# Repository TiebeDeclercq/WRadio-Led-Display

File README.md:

# WRadio LED Display
A custom-built LED display that showcases WRadio's logo with smooth animations and interactive brightness/animation controls via a built-in button.

## Hardware Overview
The design features a straightforward schematic controlled by an STM32F030F4P6TR microcontroller, providing reliable performance in a compact form factor and a cheap price.

## Assembly Instructions
### PCB Assembly
For soldering, refer to the included BOM (Bill of Materials) file. All components are 0805 package size for easy assembly.

### 3D Printed Enclosure
The enclosure consists of two main parts:

**Top Piece:** Requires a multi-color 3D printer or filament switching capability. The first few layers must be printed in white filament to allow proper light diffusion through the logo.

**Bottom Piece:** Choose between the standard base or the angled standing version depending on your preferred display orientation.

### Final Assembly
To assemble the enclosure, simply click the top and bottom pieces together. Make sure the USB-C port on the PCB aligns properly with the corresponding hole in the 3D printed top piece for easy access to power and programming.

## Software
The firmware is developed using STM32CubeIDE and includes:
- Multiple animation modes
- Adjustable brightness levels
- Save system in flash memory
- Button-controlled user interface

## Getting Started
1. Assemble the PCB using the provided BOM
2. 3D print the enclosure parts
3. Insert the PCB into the top piece, ensuring USB-C port alignment
4. Click the top piece into place
5. Flash the firmware using STM32CubeIDE
6. Enjoy your custom WRadio LED display!

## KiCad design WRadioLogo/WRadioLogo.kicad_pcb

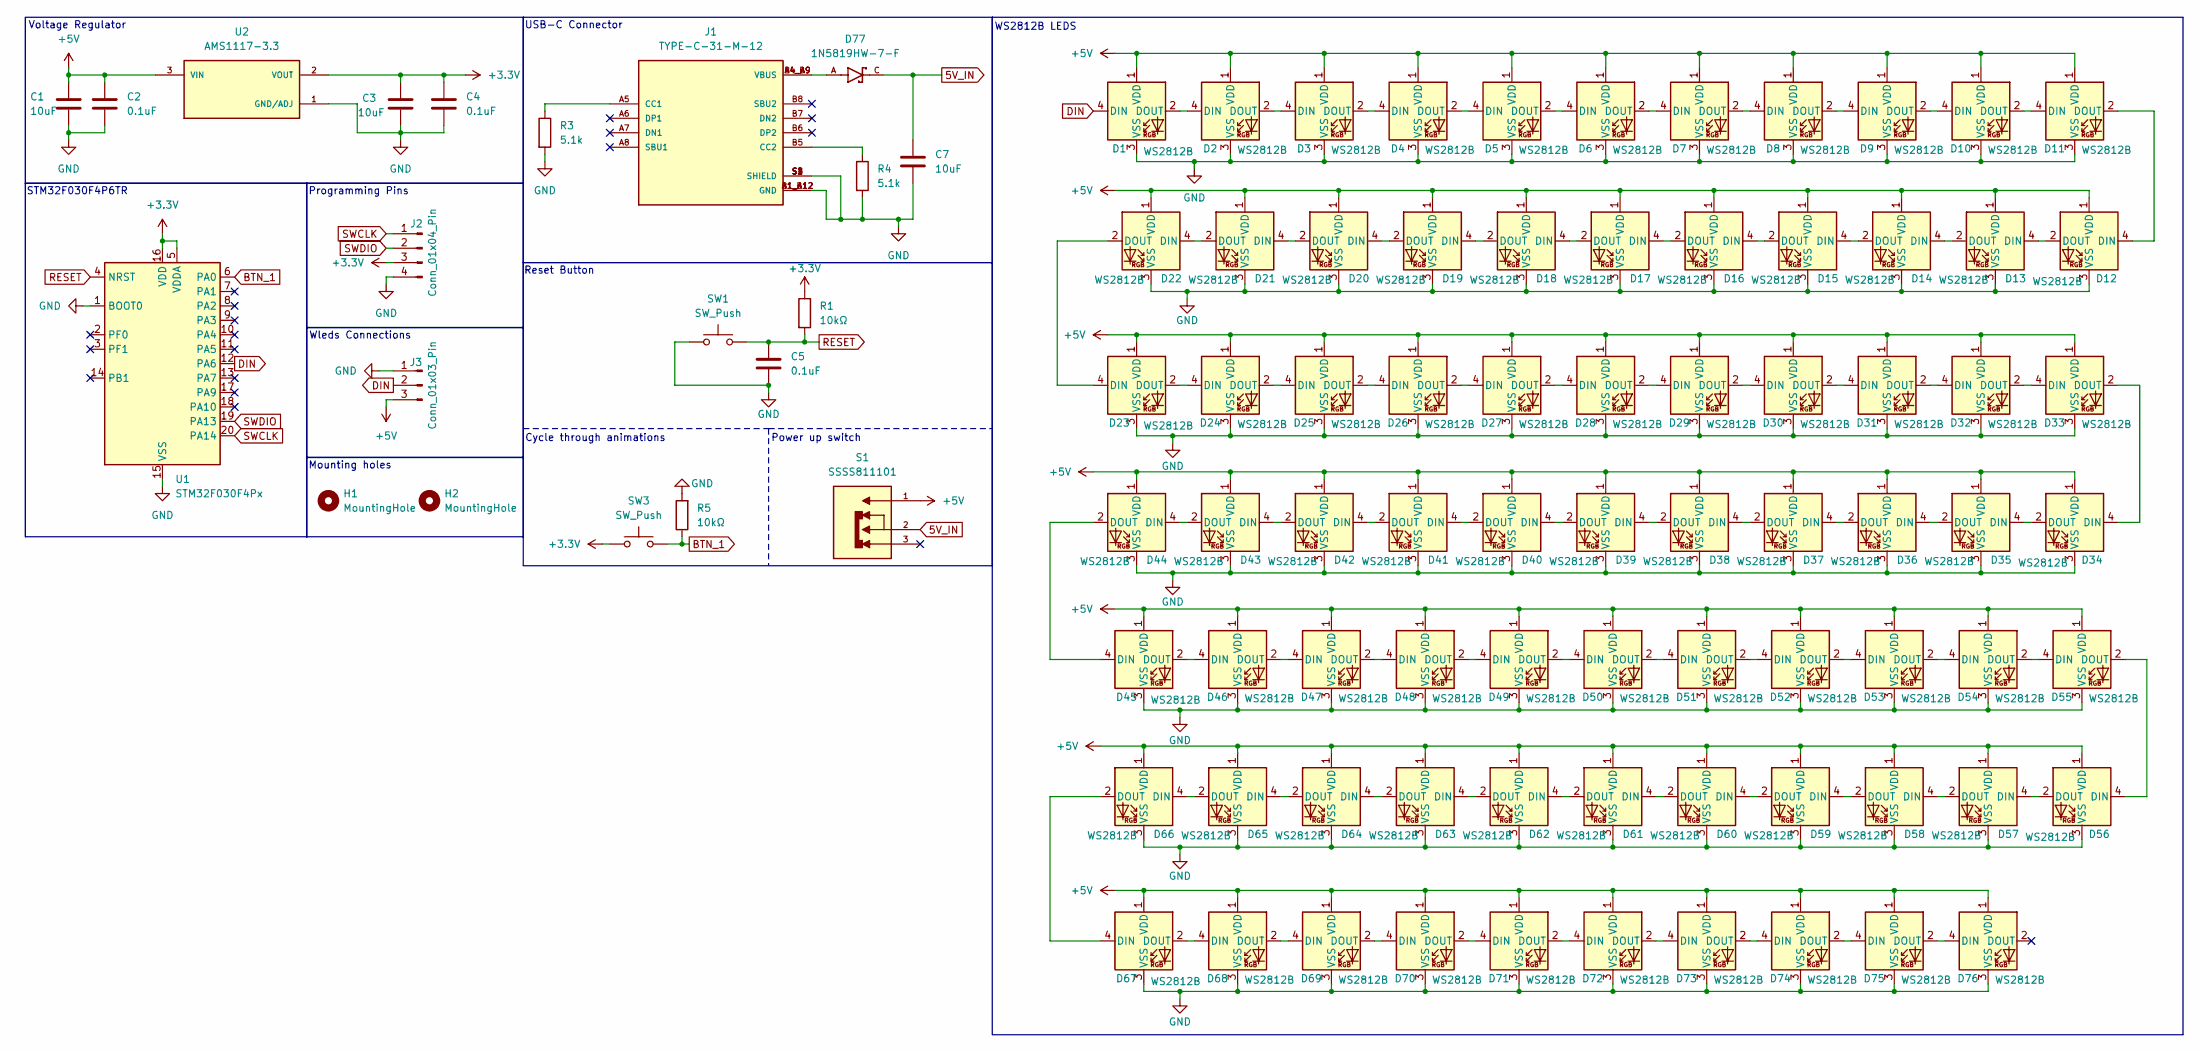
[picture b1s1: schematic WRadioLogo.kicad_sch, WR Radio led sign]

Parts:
C1, C3, C7: 10uF; C_0805_2012Metric_Pad1.18x1.45mm_HandSolder
C2, C4, C5: 0.1uF; C_0805_2012Metric_Pad1.18x1.45mm_HandSolder
D1, D2, D3, D4, D5, D6, D7, D8, D9, D10, D11, D12, D13, D14, D15, D16, D17, D18, D19, D20, D21, D22, D23, D24, D25, D26, D27, D28, D29, D30, D31, D32, D33, D34, D35, D36, D37, D38, D39, D40, D41, D42, D43, D44, D45, D46, D47, D48, D49, D50, D51, D52, D53, D54, D55, D56, D57, D58, D59, D60, D61, D62, D63, D64, D65, D66, D67, D68, D69, D70, D71, D72, D73, D74, D75, D76: WS2812B; LED_WS2812B_PLCC4_5.0x5.0mm_P3.2mm
D77: 1N5819HW-7-F; SOD3715X145N; PARTREV 18-2
H1, H2: MountingHole; MountingHole_3.2mm_M3
J1: TYPE-C-31-M-12; HRO_TYPE-C-31-M-12; PARTREV 2020.12.08
J2: Conn_01x04_Pin; PinHeader_1x04_P2.54mm_Vertical
J3: Conn_01x03_Pin; PinHeader_1x03_P2.54mm_Vertical
R1, R5: 10kΩ; R_0805_2012Metric_Pad1.20x1.40mm_HandSolder
R3, R4: 5.1k; R_0805_2012Metric_Pad1.20x1.40mm_HandSolder
S1: SSSS811101; SW_SSSS811101; PARTREV N/A
SW1: SW_Push; SW_SPST_FSMSM
SW3: SW_Push; Panasonic_EVQPUJ_EVQPUA
U1: STM32F030F4Px; TSSOP-20_4.4x6.5mm_P0.65mm
U2: AMS1117-3.3; SOT229P700X180-4N; PARTREV N/A

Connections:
5V_IN: C7.1, D77.C, S1.2
+3.3V: C3.1, C4.1, J2.3, R1.1, SW3.1, U1.5 (VDDA), U1.16 (VDD), U2.2 (VOUT)
+5V: C1.1, C2.1, D1.1 (VDD), D2.1 (VDD), D3.1 (VDD), D4.1 (VDD), D5.1 (VDD), D6.1 (VDD), D7.1 (VDD), D8.1 (VDD), D9.1 (VDD), D10.1 (VDD), D11.1 (VDD), D12.1 (VDD), D13.1 (VDD), D14.1 (VDD), D15.1 (VDD), D16.1 (VDD), D17.1 (VDD), D18.1 (VDD), D19.1 (VDD), D20.1 (VDD), D21.1 (VDD), D22.1 (VDD), D23.1 (VDD), D24.1 (VDD), D25.1 (VDD), D26.1 (VDD), D27.1 (VDD), D28.1 (VDD), D29.1 (VDD), D30.1 (VDD), D31.1 (VDD), D32.1 (VDD), D33.1 (VDD), D34.1 (VDD), D35.1 (VDD), D36.1 (VDD), D37.1 (VDD), D38.1 (VDD), D39.1 (VDD), D40.1 (VDD), D41.1 (VDD), D42.1 (VDD), D43.1 (VDD), D44.1 (VDD), D45.1 (VDD), D46.1 (VDD), D47.1 (VDD), D48.1 (VDD), D49.1 (VDD), D50.1 (VDD), D51.1 (VDD), D52.1 (VDD), D53.1 (VDD), D54.1 (VDD), D55.1 (VDD), D56.1 (VDD), D57.1 (VDD), D58.1 (VDD), D59.1 (VDD), D60.1 (VDD), D61.1 (VDD), D62.1 (VDD), D63.1 (VDD), D64.1 (VDD), D65.1 (VDD), D66.1 (VDD), D67.1 (VDD), D68.1 (VDD), D69.1 (VDD), D70.1 (VDD), D71.1 (VDD), D72.1 (VDD), D73.1 (VDD), D74.1 (VDD), D75.1 (VDD), D76.1 (VDD), J3.3, S1.1, U2.3 (VIN)
BTN_1: R5.1, SW3.2, U1.6 (PA0)
DIN: D1.4 (DIN), J3.2, U1.12 (PA6)
GND: C1.2, C2.2, C3.2, C4.2, C5.2, C7.2, D1.3 (VSS), D2.3 (VSS), D3.3 (VSS), D4.3 (VSS), D5.3 (VSS), D6.3 (VSS), D7.3 (VSS), D8.3 (VSS), D9.3 (VSS), D10.3 (VSS), D11.3 (VSS), D12.3 (VSS), D13.3 (VSS), D14.3 (VSS), D15.3 (VSS), D16.3 (VSS), D17.3 (VSS), D18.3 (VSS), D19.3 (VSS), D20.3 (VSS), D21.3 (VSS), D22.3 (VSS), D23.3 (VSS), D24.3 (VSS), D25.3 (VSS), D26.3 (VSS), D27.3 (VSS), D28.3 (VSS), D29.3 (VSS), D30.3 (VSS), D31.3 (VSS), D32.3 (VSS), D33.3 (VSS), D34.3 (VSS), D35.3 (VSS), D36.3 (VSS), D37.3 (VSS), D38.3 (VSS), D39.3 (VSS), D40.3 (VSS), D41.3 (VSS), D42.3 (VSS), D43.3 (VSS), D44.3 (VSS), D45.3 (VSS), D46.3 (VSS), D47.3 (VSS), D48.3 (VSS), D49.3 (VSS), D50.3 (VSS), D51.3 (VSS), D52.3 (VSS), D53.3 (VSS), D54.3 (VSS), D55.3 (VSS), D56.3 (VSS), D57.3 (VSS), D58.3 (VSS), D59.3 (VSS), D60.3 (VSS), D61.3 (VSS), D62.3 (VSS), D63.3 (VSS), D64.3 (VSS), D65.3 (VSS), D66.3 (VSS), D67.3 (VSS), D68.3 (VSS), D69.3 (VSS), D70.3 (VSS), D71.3 (VSS), D72.3 (VSS), D73.3 (VSS), D74.3 (VSS), D75.3 (VSS), D76.3 (VSS), J1.A1_B12 (GND), J1.B1_A12 (GND), J1.S1 (SHIELD), J1.S2 (SHIELD), J1.S3 (SHIELD), J1.S4 (SHIELD), J2.4, J3.1, R3.2, R4.2, R5.2, SW1.1, U1.1 (BOOT0), U1.15 (VSS), U2.1 (GND/ADJ)
unnamed: D1.2 (DOUT), D2.4 (DIN)
unnamed: D2.2 (DOUT), D3.4 (DIN)
unnamed: D3.2 (DOUT), D4.4 (DIN)
unnamed: D4.2 (DOUT), D5.4 (DIN)
unnamed: D5.2 (DOUT), D6.4 (DIN)
unnamed: D6.2 (DOUT), D7.4 (DIN)
unnamed: D7.2 (DOUT), D8.4 (DIN)
unnamed: D8.2 (DOUT), D9.4 (DIN)
unnamed: D9.2 (DOUT), D10.4 (DIN)
unnamed: D10.2 (DOUT), D11.4 (DIN)
unnamed: D11.2 (DOUT), D12.4 (DIN)
unnamed: D12.2 (DOUT), D13.4 (DIN)
unnamed: D13.2 (DOUT), D14.4 (DIN)
unnamed: D14.2 (DOUT), D15.4 (DIN)
unnamed: D15.2 (DOUT), D16.4 (DIN)
unnamed: D16.2 (DOUT), D17.4 (DIN)
unnamed: D17.2 (DOUT), D18.4 (DIN)
unnamed: D18.2 (DOUT), D19.4 (DIN)
unnamed: D19.2 (DOUT), D20.4 (DIN)
unnamed: D20.2 (DOUT), D21.4 (DIN)
unnamed: D21.2 (DOUT), D22.4 (DIN)
unnamed: D22.2 (DOUT), D23.4 (DIN)
unnamed: D23.2 (DOUT), D24.4 (DIN)
unnamed: D24.2 (DOUT), D25.4 (DIN)
unnamed: D25.2 (DOUT), D26.4 (DIN)
unnamed: D26.2 (DOUT), D27.4 (DIN)
unnamed: D27.2 (DOUT), D28.4 (DIN)
unnamed: D28.2 (DOUT), D29.4 (DIN)
unnamed: D29.2 (DOUT), D30.4 (DIN)
unnamed: D30.2 (DOUT), D31.4 (DIN)
unnamed: D31.2 (DOUT), D32.4 (DIN)
unnamed: D32.2 (DOUT), D33.4 (DIN)
unnamed: D33.2 (DOUT), D34.4 (DIN)
unnamed: D34.2 (DOUT), D35.4 (DIN)
unnamed: D35.2 (DOUT), D36.4 (DIN)
unnamed: D36.2 (DOUT), D37.4 (DIN)
unnamed: D37.2 (DOUT), D38.4 (DIN)
unnamed: D38.2 (DOUT), D39.4 (DIN)
unnamed: D39.2 (DOUT), D40.4 (DIN)
unnamed: D40.2 (DOUT), D41.4 (DIN)
unnamed: D41.2 (DOUT), D42.4 (DIN)
unnamed: D42.2 (DOUT), D43.4 (DIN)
unnamed: D43.2 (DOUT), D44.4 (DIN)
unnamed: D44.2 (DOUT), D45.4 (DIN)
unnamed: D45.2 (DOUT), D46.4 (DIN)
unnamed: D46.2 (DOUT), D47.4 (DIN)
unnamed: D47.2 (DOUT), D48.4 (DIN)
unnamed: D48.2 (DOUT), D49.4 (DIN)
unnamed: D49.2 (DOUT), D50.4 (DIN)
unnamed: D50.2 (DOUT), D51.4 (DIN)
unnamed: D51.2 (DOUT), D52.4 (DIN)
unnamed: D52.2 (DOUT), D53.4 (DIN)
unnamed: D53.2 (DOUT), D54.4 (DIN)
unnamed: D54.2 (DOUT), D55.4 (DIN)
unnamed: D55.2 (DOUT), D56.4 (DIN)
unnamed: D56.2 (DOUT), D57.4 (DIN)
unnamed: D57.2 (DOUT), D58.4 (DIN)
unnamed: D58.2 (DOUT), D59.4 (DIN)
unnamed: D59.2 (DOUT), D60.4 (DIN)
unnamed: D60.2 (DOUT), D61.4 (DIN)
unnamed: D61.2 (DOUT), D62.4 (DIN)
unnamed: D62.2 (DOUT), D63.4 (DIN)
unnamed: D63.2 (DOUT), D64.4 (DIN)
unnamed: D64.2 (DOUT), D65.4 (DIN)
unnamed: D65.2 (DOUT), D66.4 (DIN)
unnamed: D66.2 (DOUT), D67.4 (DIN)
unnamed: D67.2 (DOUT), D68.4 (DIN)
unnamed: D68.2 (DOUT), D69.4 (DIN)
unnamed: D69.2 (DOUT), D70.4 (DIN)
unnamed: D70.2 (DOUT), D71.4 (DIN)
unnamed: D71.2 (DOUT), D72.4 (DIN)
unnamed: D72.2 (DOUT), D73.4 (DIN)
unnamed: D73.2 (DOUT), D74.4 (DIN)
unnamed: D74.2 (DOUT), D75.4 (DIN)
unnamed: D75.2 (DOUT), D76.4 (DIN)
unnamed: D77.A, J1.A4_B9 (VBUS), J1.B4_A9 (VBUS)
unnamed: J1.A5 (CC1), R3.1
unnamed: J1.B5 (CC2), R4.1
RESET: C5.1, R1.2, SW1.2, U1.4 (NRST)
SWCLK: J2.1, U1.20 (PA14)
SWDIO: J2.2, U1.19 (PA13)

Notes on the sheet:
Voltage Regulator
Wleds Connections
Programming Pins
USB-C Connector
Reset Button
Cycle through animations
Power up switch
WS2812B LEDS
Mounting holes
STM32F030F4P6TR

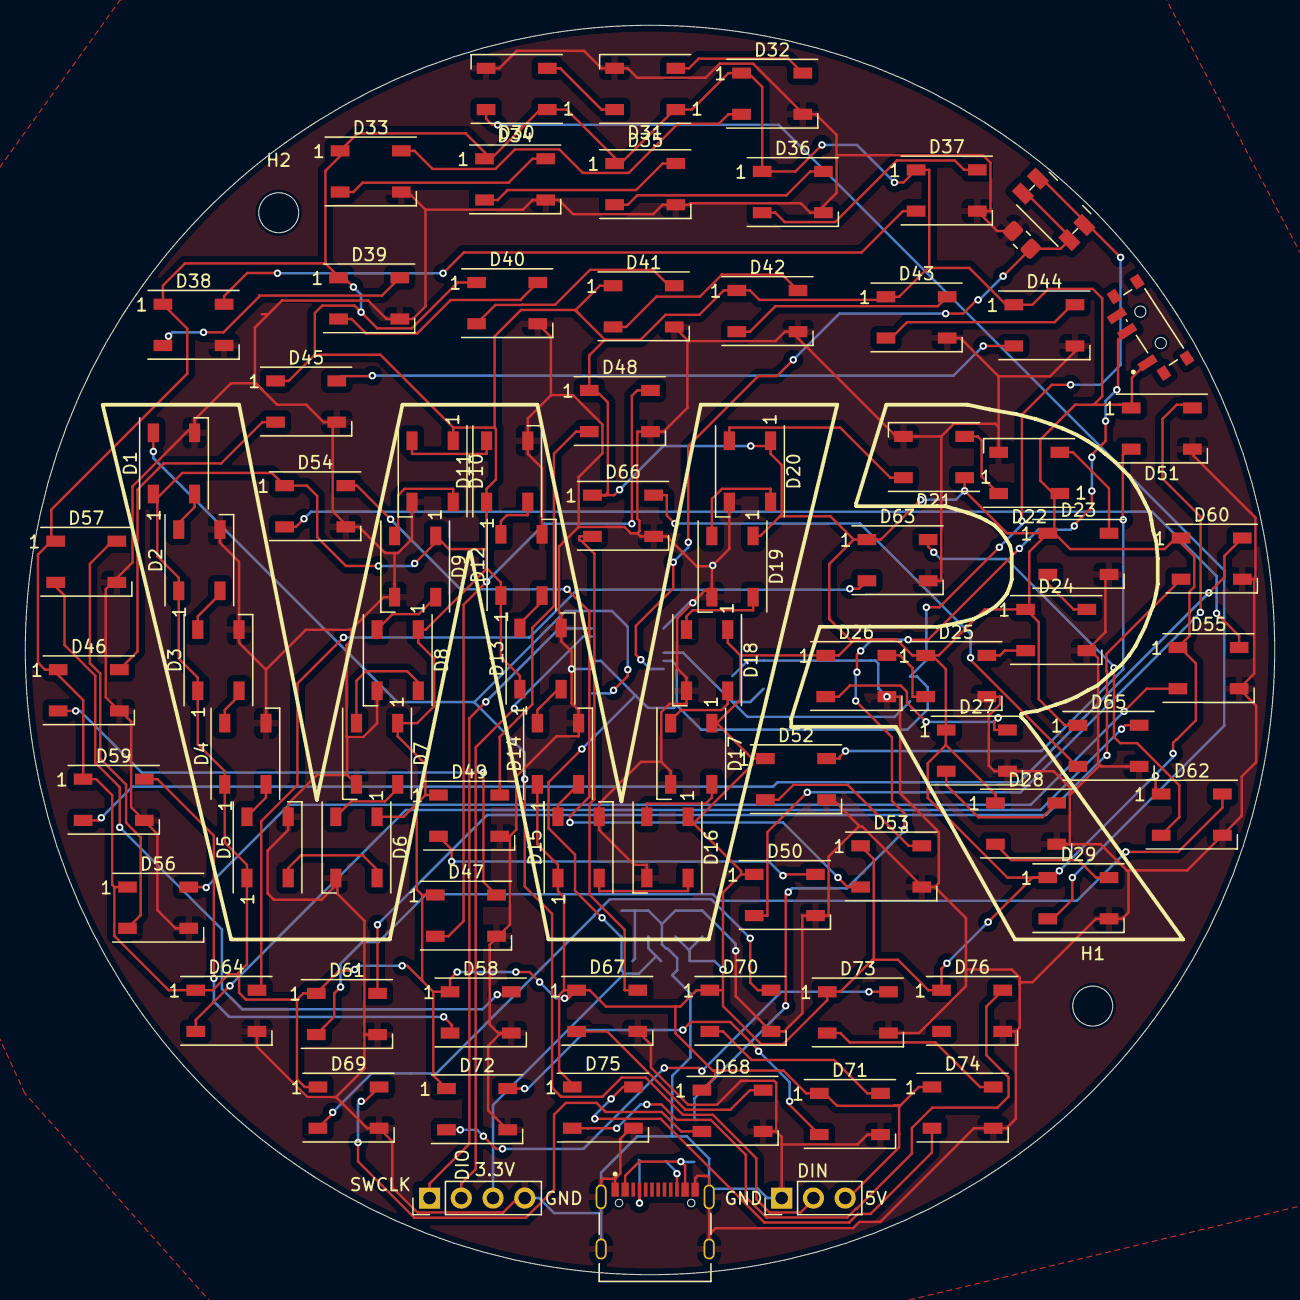
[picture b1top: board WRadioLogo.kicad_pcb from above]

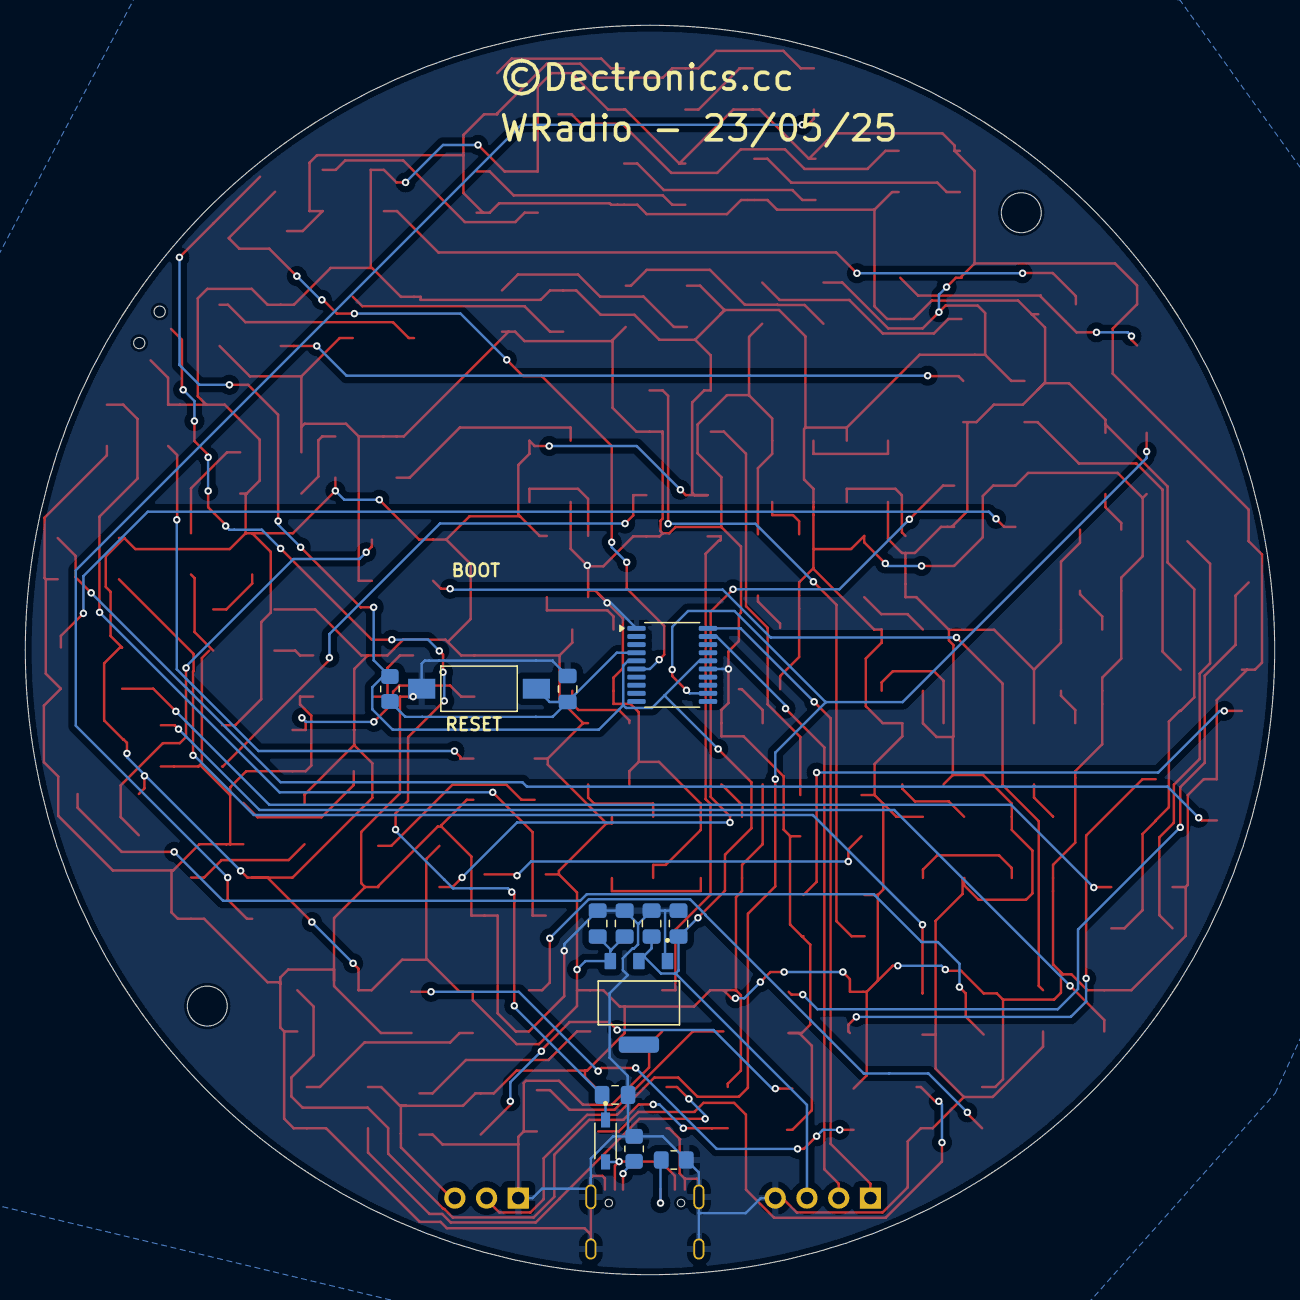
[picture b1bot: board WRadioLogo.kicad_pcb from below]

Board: 2 copper layers, 100.0 x 100.0 mm, 97 parts (13 on the bottom side), 87 nets.

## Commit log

2025-05-22 init
2025-05-22 NOTWORKING
2025-05-22 IT WORKSS
2025-05-22 NOG 840 bytes
2025-05-22 V1 PCB
2025-05-24 nieuwe patronen + helderheid wip
2025-05-24 Saves brightness
2025-05-24 fix brightness
2025-05-25 afbeeldingen+stls
2025-09-08 Deleted double ref

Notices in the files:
WRadioLogo/WRadioLogo.kicad_pcb:
©Dectronics.cc
